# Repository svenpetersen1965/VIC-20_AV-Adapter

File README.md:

# VIC-20 A/V-Adapter
An Adapter for connecting the Commodore VIC-20 to video equipment with off the shelve A/V-cables.

A 3D printed case and a case label are provided in this repository.

The A/V-adapter was tested with
* the Commodore VIC-20
* the Commodore C16
* the Commodore C64
* the Atari 800XL

It is not suitable for the Commodore C128
# BOM Value
The BOM value of Rev. 1, without the 3D printed case and label is 9.50€ (01.11.2021, values obtained from Reichelt.de). The Lumberg connectors are more expensive from other suppliers.

# Rev. 2
The Lumberg BTOR1 RCA jacks were obsolete and replaced with CUI Inc. RCJ-02*. This also requires a different bottom shell of the 3D-printed case. There are Keystome RCA jacks, that fit the same footprint (they are more expensive). See the BOM Rev. 2

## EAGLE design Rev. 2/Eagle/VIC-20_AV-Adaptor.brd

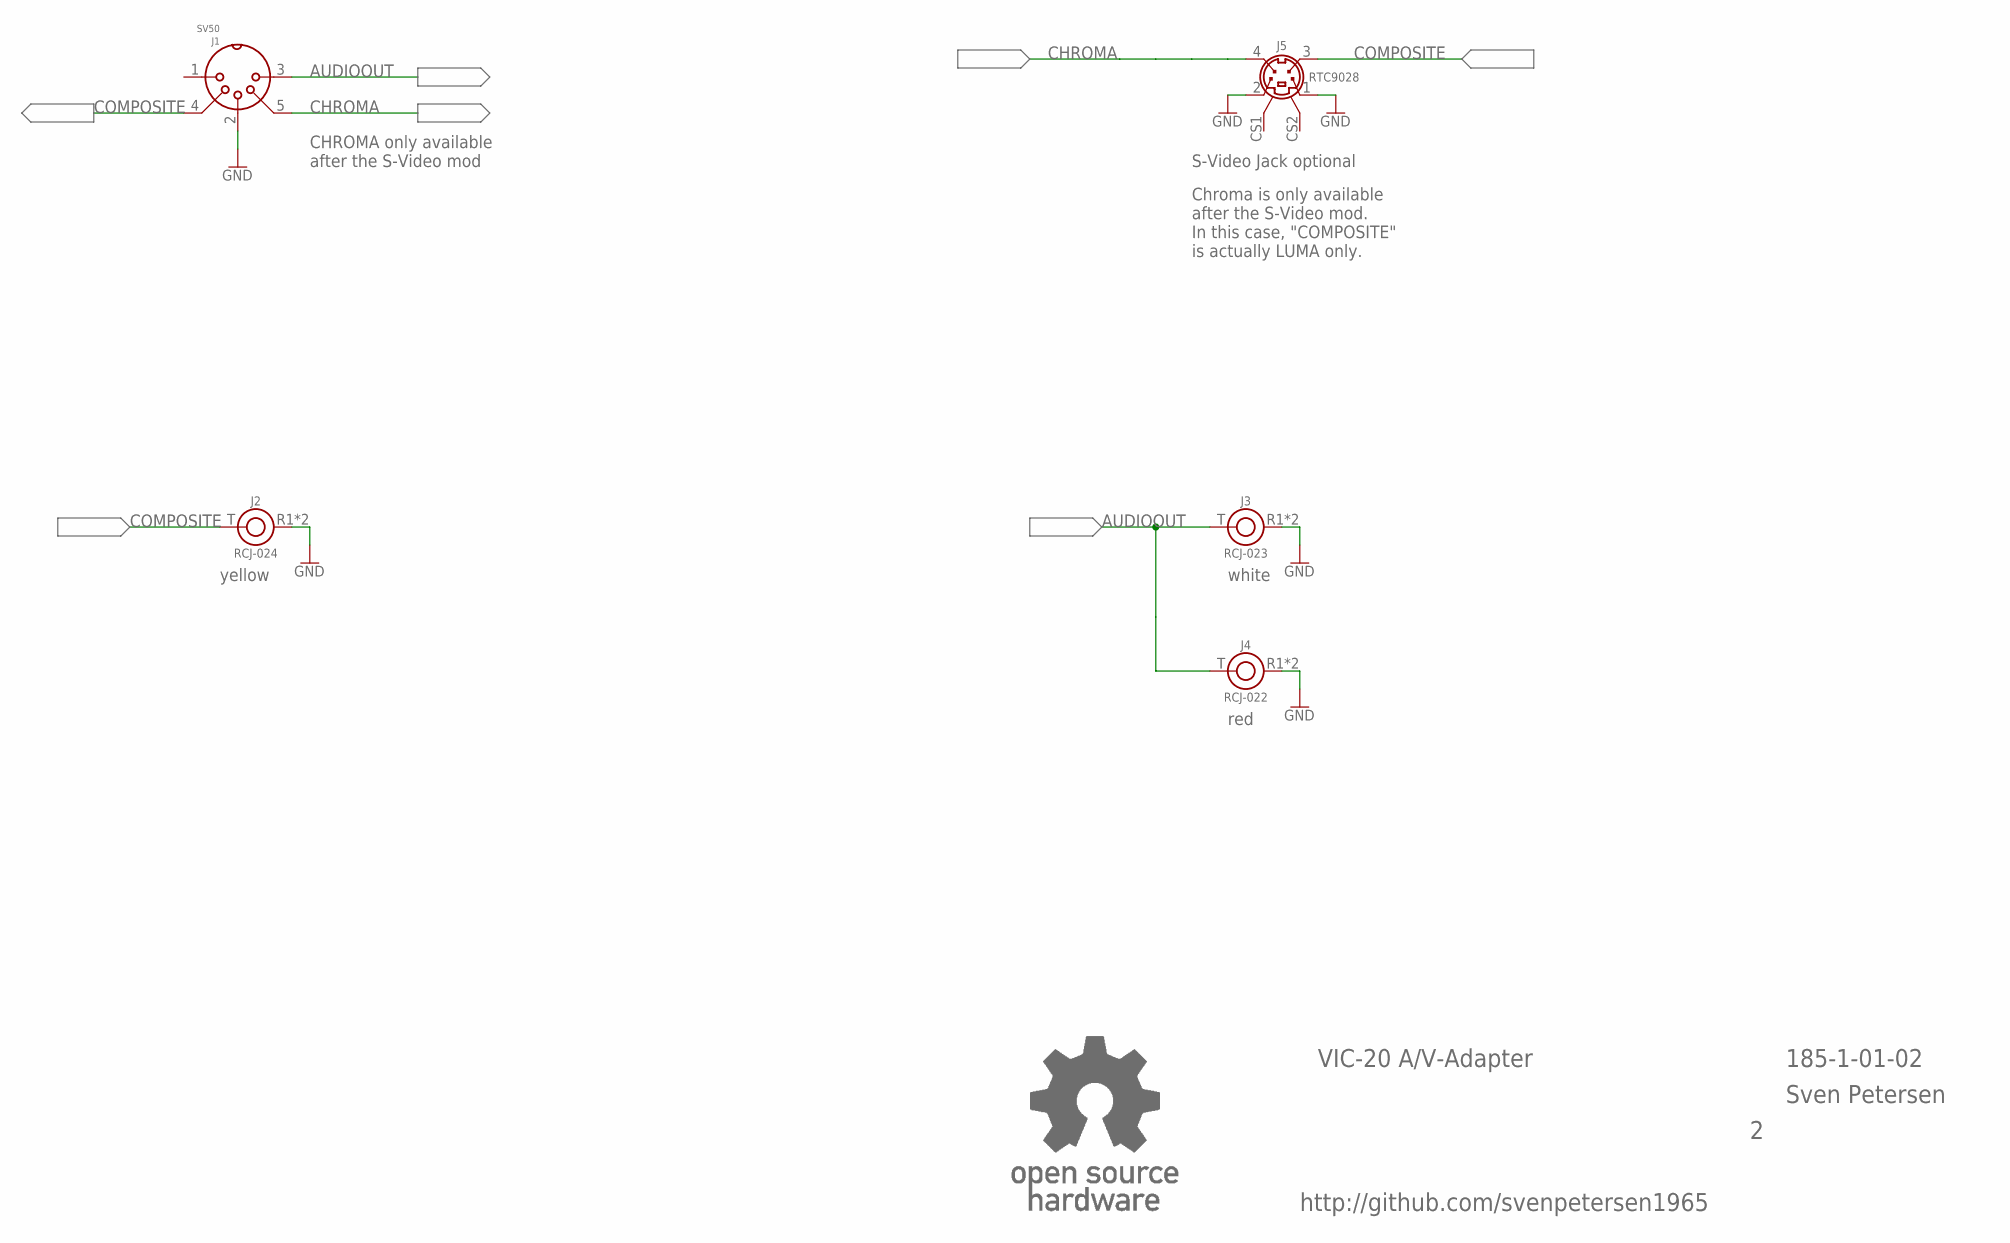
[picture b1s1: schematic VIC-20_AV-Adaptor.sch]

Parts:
J1: SV50; SV50_INNER
J2: RCJ-024; RCJ-02X
J3: RCJ-023; RCJ-02X
J4: RCJ-022; RCJ-02X
J5: RTC9028; MINIDIN4_V
U$25: OPEN_SOURCE_HW; OPENHW

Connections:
AUDIOOUT: J1.3, J3.T, J4.T
CHROMA: J1.5, J5.4
COMPOSITE: J1.4, J2.T, J5.3
GND: J1.2, J2.R1 (R), J2.R2 (R), J3.R1 (R), J3.R2 (R), J4.R1 (R), J4.R2 (R), J5.1, J5.2

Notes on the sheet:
VIC-20 A/V-Adapter
185-1-01-02
Sven Petersen
http://github.com/svenpetersen1965
CHROMA only available after the S-Video mod
S-Video Jack optional
Chroma is only available after the S-Video mod. In this case, "COMPOSITE" is actually LUMA only.
white
red
yellow

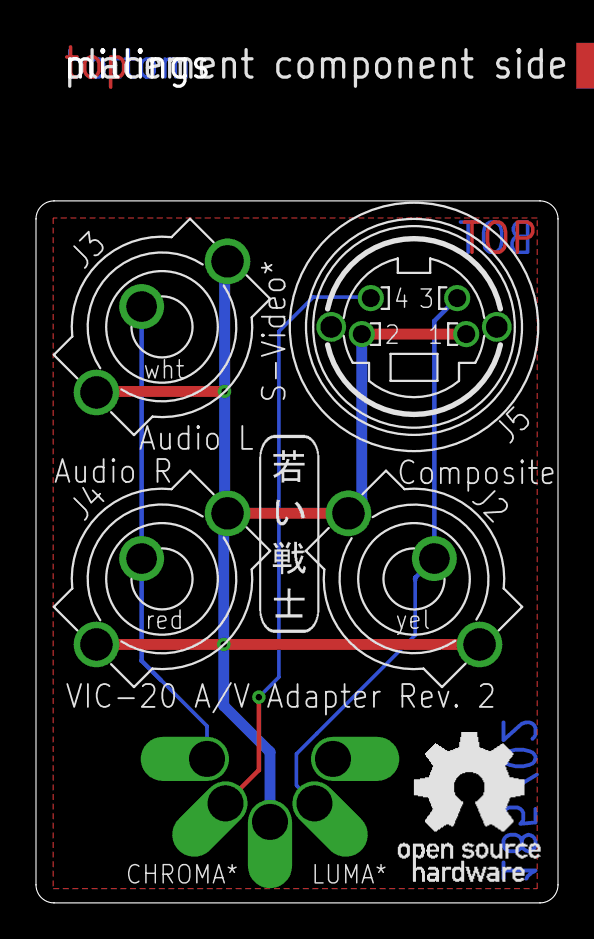
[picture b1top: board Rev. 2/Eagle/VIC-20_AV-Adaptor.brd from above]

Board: 2 copper layers, 29.0 x 48.2 mm, 9 parts (1 on the bottom side), 4 nets.

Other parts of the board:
U$22: 2LAYER
U$23: SVEN_TAG
U$24: PCB-TITLE/

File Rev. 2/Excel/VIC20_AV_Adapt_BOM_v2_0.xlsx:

VIC-20 A/V-Adaptor Rev. 2
Bill of Material Rev. 2.0
Pos. | Qty | Value | Footprint | Ref.-No. | Comment
1 | 1 | 185-2-01-02 | 2 Layer | PCB Rev. 2 | 2 layer, Cu 35µ, HASL, 39.0mm x 29.0mm, 1.6mm FR4
2 | 1 | RCJ-022 | RCJ-02X | J4 | CUI Inc., RCA jack, vertical, red. Mouser: 490-RCJ-022, Digikey: CP-1407-ND. Al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
3 | 1 | RCJ-023 | RCJ-02X | J3 | CUI Inc., RCA jack, vertical, white. Mouser: 490-RCJ-023, Digikey: CP-1408-ND. 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
4 | 1 | RCJ-024 | RCJ-02X | J2 | CUI Inc., RCA jack, vertical, yellow. Mouser: 490-RCJ-024, Digikey: CP-1409-ND.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
5 | 1 | SV50 | SV50_INNER | J1 | Inner part of Lumberg SV 50 (SV 50-8), e.G. Reichelt: LUM SV 50, Newark: 82AH33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
6 | 1 | solder bridge |  | JP1 | structure on PCB, close for proper operation
7 | 1 | RTC9028 | MINIDIN4_V | J5 | Mini-DIN, 4p, vertical. Not required for 5-pin and VIC-20. E.g. AliExpress:
8 |  |  |  |  | RTConnector: RTC9028
9 |  |  |  |  | ebay.de
 |  | Rev. 1.0 ® Rev. 2.0
Pos. | 1 | pcb revision
Pos. | 2 | new RCA jack
Pos. | 3 | new RCA jack
Pos. | 4 | new RCA jack

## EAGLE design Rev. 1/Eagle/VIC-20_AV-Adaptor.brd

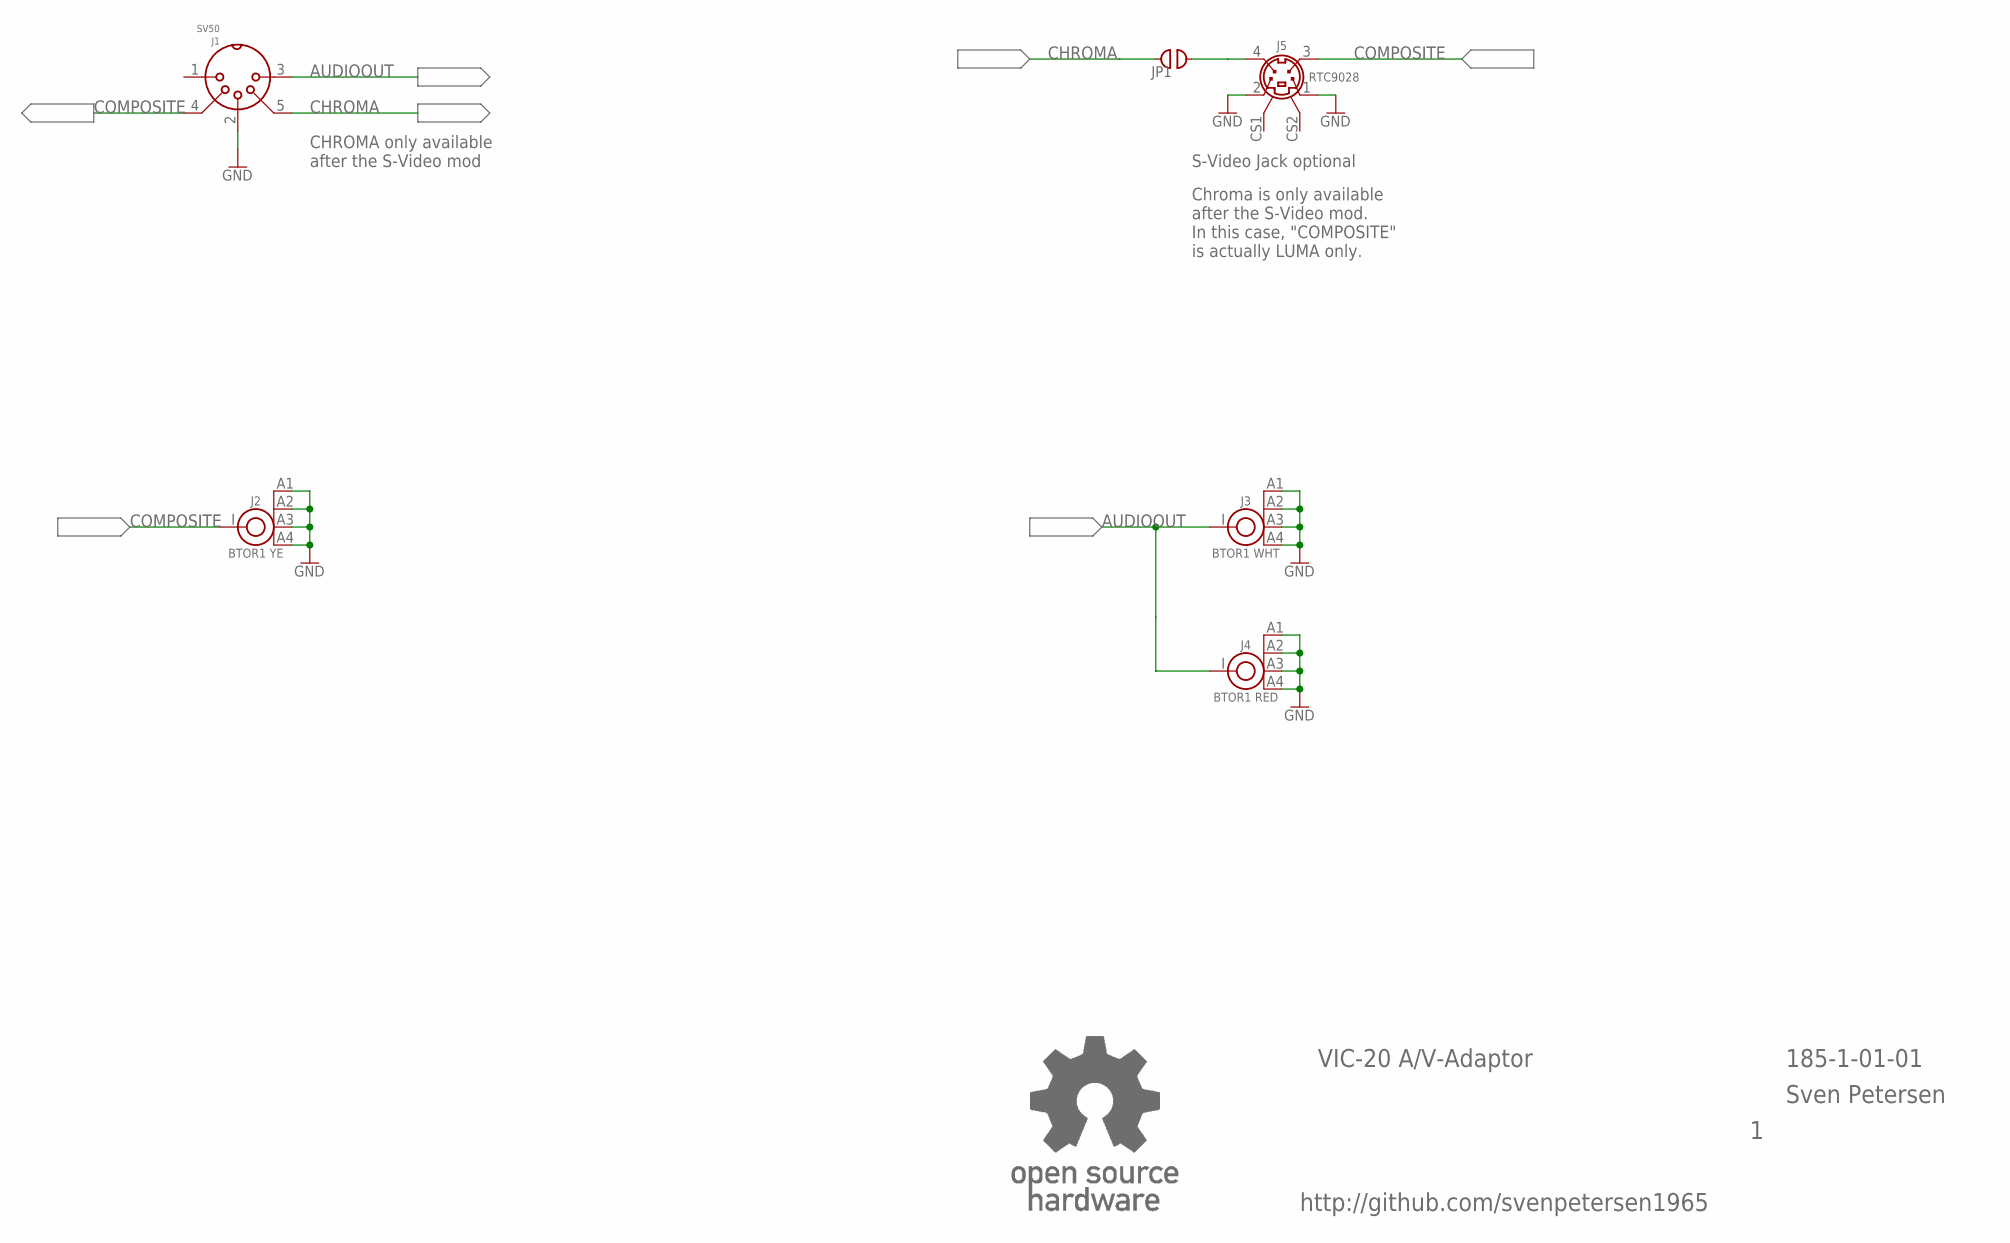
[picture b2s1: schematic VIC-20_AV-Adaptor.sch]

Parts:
J1: SV50; SV50_INNER
J2: BTOR1 YE; BTOR1
J3: BTOR1 WHT; BTOR1
J4: BTOR1 RED; BTOR1
J5: RTC9028; MINIDIN4_V
JP1: COMBI_2P; COMBI-2P
U$25: OPEN_SOURCE_HW; OPENHW

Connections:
AUDIOOUT: J1.3, J3.I, J4.I
CHROMA: J1.5, JP1.1
COMPOSITE: J1.4, J2.I, J5.3
GND: J1.2, J2.A1, J2.A2, J2.A3, J2.A4, J3.A1, J3.A2, J3.A3, J3.A4, J4.A1, J4.A2, J4.A3, J4.A4, J5.1, J5.2
unnamed: J5.4, JP1.2

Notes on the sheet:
VIC-20 A/V-Adaptor
185-1-01-01
Sven Petersen
http://github.com/svenpetersen1965
CHROMA only available after the S-Video mod
S-Video Jack optional
Chroma is only available after the S-Video mod. In this case, "COMPOSITE" is actually LUMA only.

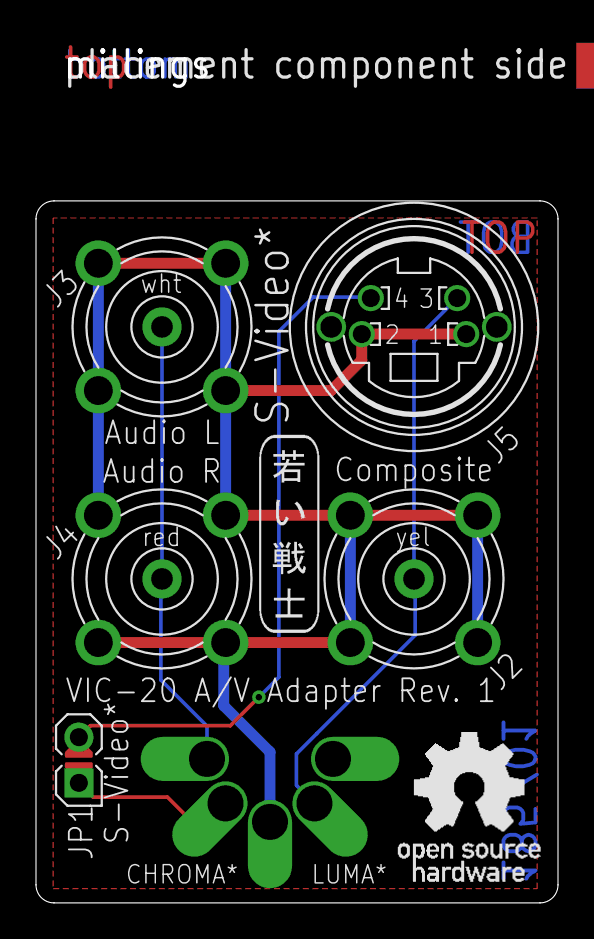
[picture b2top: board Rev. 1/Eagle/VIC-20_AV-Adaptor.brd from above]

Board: 2 copper layers, 29.0 x 48.2 mm, 10 parts (1 on the bottom side), 5 nets.

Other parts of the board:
U$22: 2LAYER
U$23: SVEN_TAG
U$24: PCB-TITLE/

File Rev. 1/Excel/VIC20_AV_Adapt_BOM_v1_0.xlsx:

VIC-20 A/V-Adaptor Rev. 1
Bill of Material Rev. 1.0
Pos. | Qty | Value | Footprint | Ref.-No. | Comment
1 | 1 | 185-2-01-01 | 2 Layer | PCB Rev. 1 | 2 layer, Cu 35µ, HASL, 39.0mm x 29.0mm, 1.6mm FR4
2 | 1 | BTOR1 RED | BTOR1 | J4 | Lumberg, RCA jack, vertical, red. E.G. Reichelt LUM BTOR1 RT, Farnell: 1368644,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
3 | 1 | BTOR1 WHITE | BTOR1 | J3 | Lumberg, RCA jack, vertical, white. E.G. Reichelt LUM BTOR1 WS, Farnell: 136864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
4 | 1 | BTOR1 YELLOW | BTOR1 | J2 | Lumberg, RCA jack, vertical, yellow. E.G. Reichelt LUM BTOR1 GE, Farnell: 13686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
5 | 1 | SV50 | SV50_INNER | J1 | Inner part of Lumberg SV 50 (SV 50-8), e.G. Reichelt: LUM SV 50, Newark: 82AH33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
6 | 1 | solder bridge |  | JP1 | structure on PCB, close for proper operation
7 | 1 | RTC9028 | MINIDIN4_V | J5 | Mini-DIN, 4p, vertical. Not required for 5-pin and VIC-20. E.g. AliExpress:
8 |  |  |  |  | RTConnector: RTC9028
9 |  |  |  |  | ebay.de

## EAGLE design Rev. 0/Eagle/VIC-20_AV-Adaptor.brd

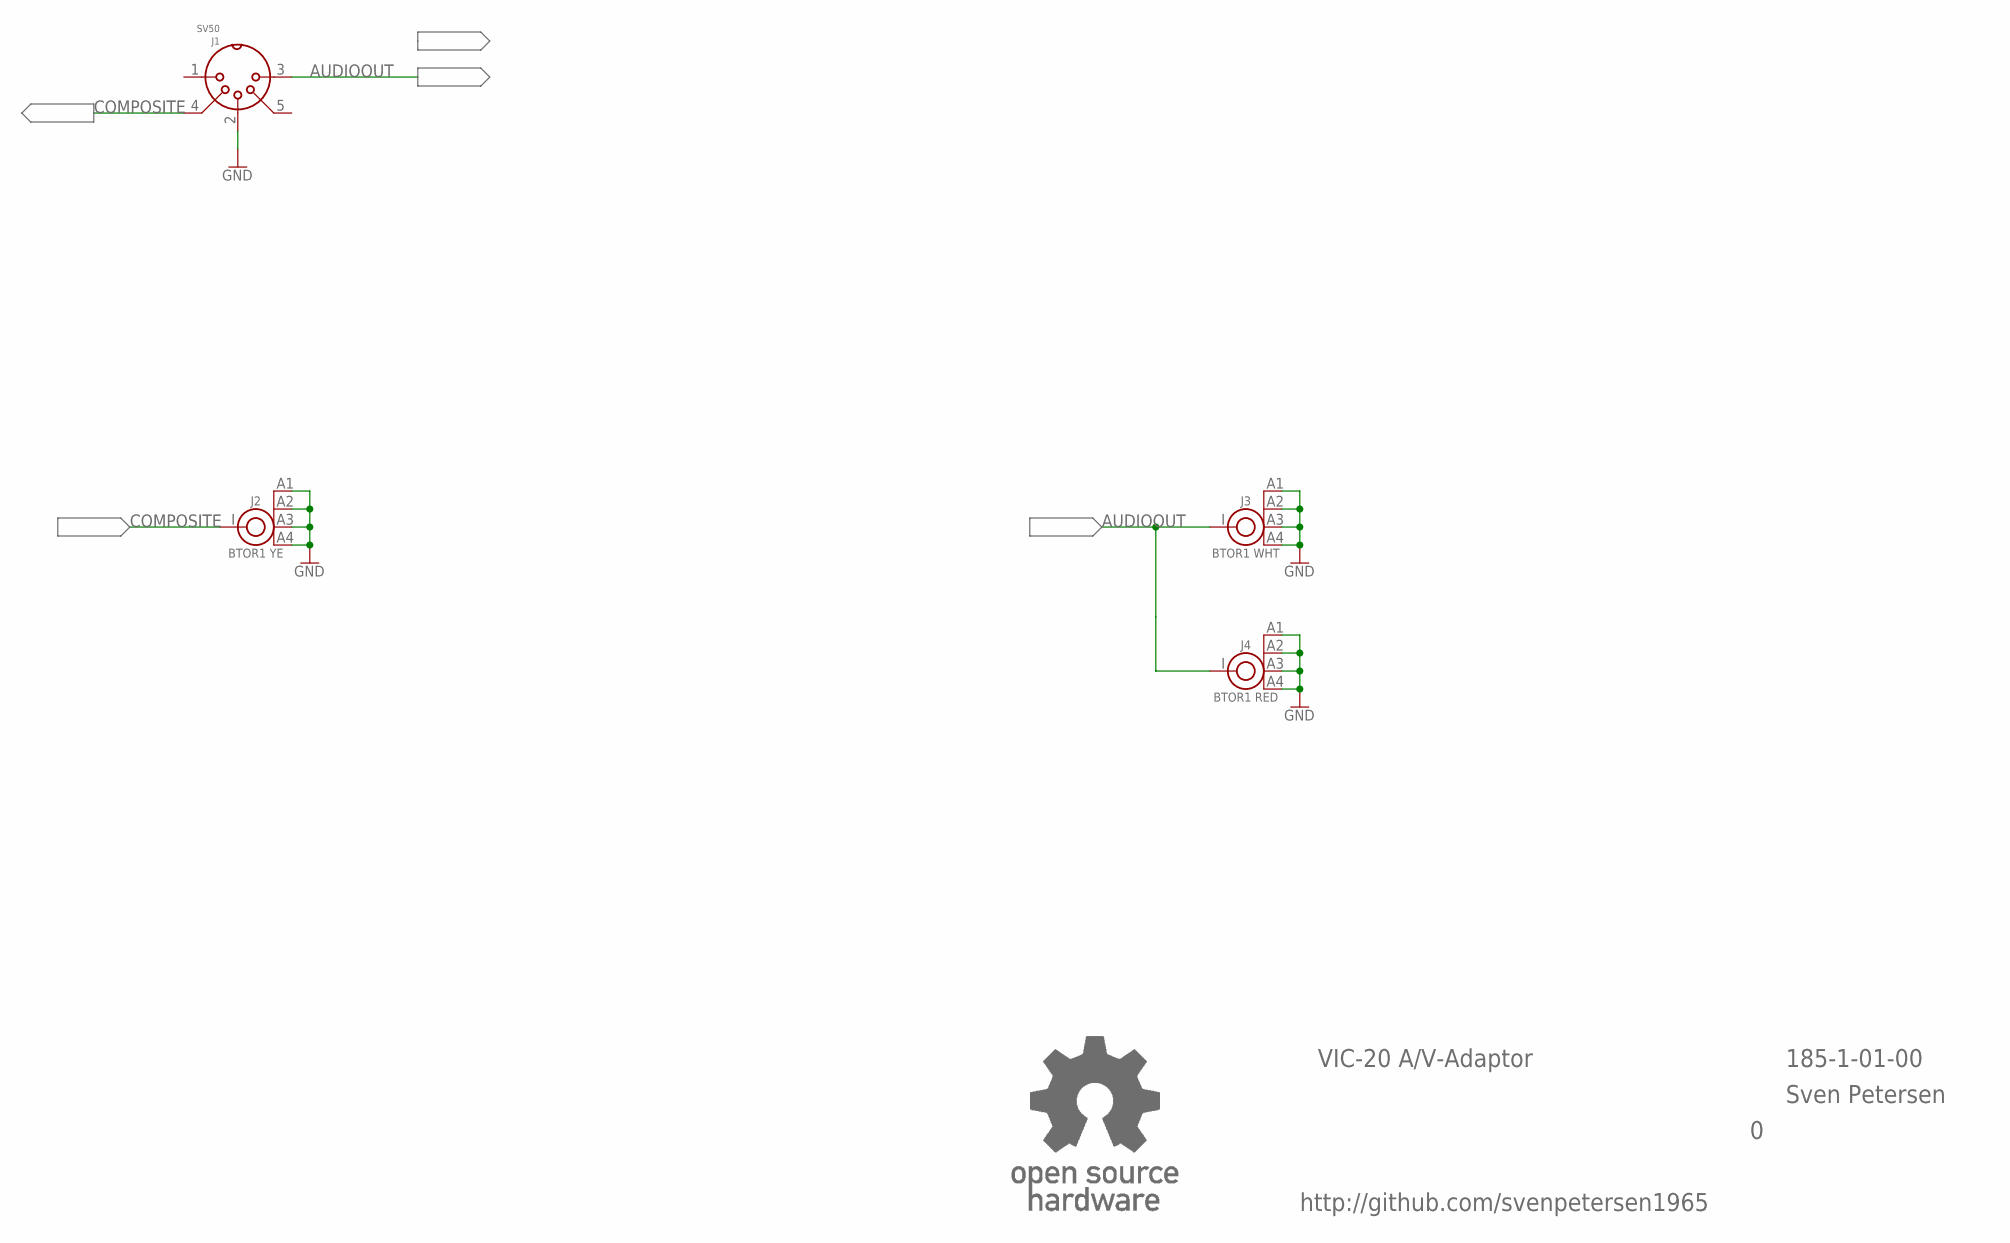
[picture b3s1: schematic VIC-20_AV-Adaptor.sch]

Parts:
J1: SV50; SV50_INNER
J2: BTOR1 YE; BTOR1
J3: BTOR1 WHT; BTOR1
J4: BTOR1 RED; BTOR1
U$25: OPEN_SOURCE_HW; OPENHW

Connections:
AUDIOOUT: J1.3, J3.I, J4.I
COMPOSITE: J1.4, J2.I
GND: J1.2, J2.A1, J2.A2, J2.A3, J2.A4, J3.A1, J3.A2, J3.A3, J3.A4, J4.A1, J4.A2, J4.A3, J4.A4

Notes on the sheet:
VIC-20 A/V-Adaptor
185-1-01-00
Sven Petersen
http://github.com/svenpetersen1965

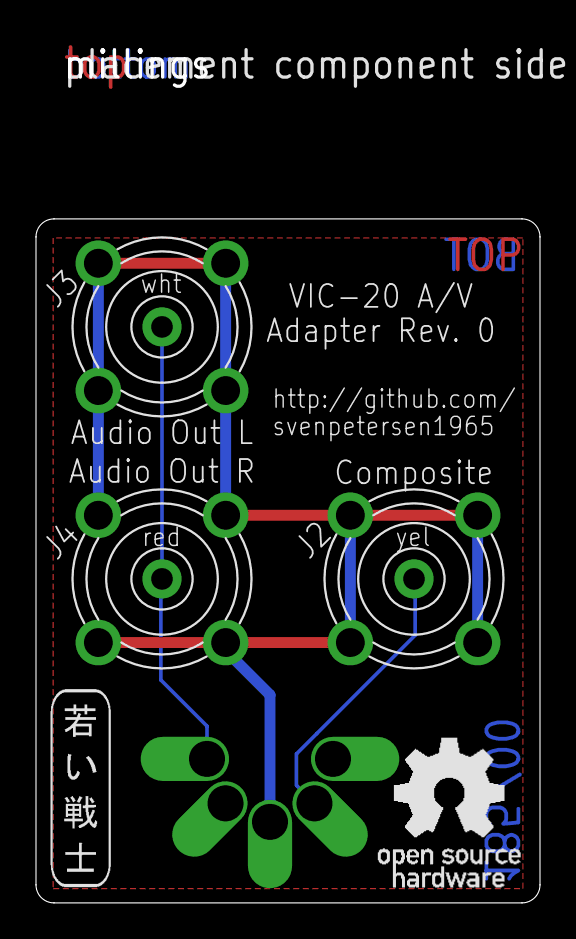
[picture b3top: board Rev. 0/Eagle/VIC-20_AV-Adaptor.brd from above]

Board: 2 copper layers, 28.0 x 48.2 mm, 8 parts (1 on the bottom side), 3 nets.

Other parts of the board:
U$22: 2LAYER
U$23: SVEN_TAG
U$24: PCB-TITLE/

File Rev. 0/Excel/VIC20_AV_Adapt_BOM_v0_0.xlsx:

VIC-20 A/V-Adaptor Rev. 0
Bill of Material Rev. 0.0
Pos. | Qty | Value | Footprint | Ref.-No. | Comment
1 | 1 | 185-2-01-00 | 2 Layer | PCB Rev. 0 | 2 layer, Cu 35µ, HASL, 38.0mm x 28.0mm, 1.6mm FR4
2 | 1 | BTOR1 RED | BTOR1 | J4 | Lumberg, RCA jack, vertical, red. E.G. Reichelt LUM BTOR1 RT, Farnell: 1368644,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
3 | 1 | BTOR1 WHITE | BTOR1 | J3 | Lumberg, RCA jack, vertical, white. E.G. Reichelt LUM BTOR1 WS, Farnell: 136864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
4 | 1 | BTOR1 YELLOW | BTOR1 | J2 | Lumberg, RCA jack, vertical, yellow. E.G. Reichelt LUM BTOR1 GE, Farnell: 13686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
5 | 1 | SV50 | SV50_INNER | J1 | Inner part of Lumberg SV 50 (SV 50-8), e.G. Reichelt: LUM SV 50, Newark: 82AH33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

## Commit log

2021-07-19 Initial release
2021-08-03 Calculation added
2021-11-01 Case Rev. 1 released
2021-11-01 PCB Rev.1 released
2021-11-01 Added calculation
2022-02-26 Gerbers removed
2022-11-10 Rev. 2 released
    Revision 2 was required due to the obsolescence of the Lumber BTOR1 RCA jacks. They were replaced by CUI Inc. type jacks with a different footprint. This also requires a different case.
2022-11-10 The case for the Rev. 2 PCB
    The PCB Rev. 2 requires a different bottom shell
